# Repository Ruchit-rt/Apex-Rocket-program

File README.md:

# art-apex
PCBs and software for ART's APEX rocket

# Contents

1. [Hardware](#Hardware)
2. [Software architecture](#SoftwareArchitecture)
3. [Next Steps](#NextSteps)

## Hardware

The flight computer for Apex consists of the following components:

1. [Tiny2040](https://shop.pimoroni.com/products/tiny-2040) microcontroller - for controlling each of the components
2. [BNO085](https://learn.adafruit.com/adafruit-9-dof-orientation-imu-fusion-breakout-bno085) 9DoF IMU - for recording and fusing flight data
3. [DPS310](https://www.infineon.com/cms/en/product/sensor/pressure-sensors/pressure-sensors-for-iot/dps310/) barometer - for recording altitude information
4. [Sim800L](https://nettigo.eu/products/sim800l-gsm-grps-module) GPRS/GSM module - for communication between the flight computer and ground team
5. [Adafruit mini GPS PA1010D](https://www.adafruit.com/product/4415) GPS module - for recovery
6. 3.7V 200maH LiPo battery - for powering the system
7. A 104 decibel speaker - for recovery

The Tiny2040 is connected to the BNO085, DPS310 and PA1010D via an I2C connection using GPIO pins 26 and 27. The Tiny2040 is connected to the Sim800L module via a UART connection using GPIO pins 4 and 5.

The SIM8000L **must** be isolated when the Tiny2040 is connected to USB, or else it will be fried.

## Software

The filesystem on board the Tiny2040 will look like this:
```
📦src
 ┣ 📂lib
 ┃ ┣ 📂adafruit_bno08x
 ┃ ┃ ┣ 📜debug.py
 ┃ ┃ ┣ 📜i2c.py
 ┃ ┃ ┗ 📜__init__.py
 ┃ ┣ 📂adafruit_bus_device
 ┃ ┃ ┣ 📜i2c_device.mpy
 ┃ ┃ ┣ 📜spi_device.mpy
 ┃ ┃ ┗ 📜__init__.py
 ┃ ┣ 📂adafruit_register
 ┃ ┃ ┣ 📜i2c_bcd_alarm.mpy
 ┃ ┃ ┣ 📜i2c_bcd_datetime.mpy
 ┃ ┃ ┣ 📜i2c_bit.mpy
 ┃ ┃ ┣ 📜i2c_bits.mpy
 ┃ ┃ ┣ 📜i2c_struct.mpy
 ┃ ┃ ┣ 📜i2c_struct_array.mpy
 ┃ ┃ ┗ 📜__init__.py
 ┃ ┣ 📜adafruit_dps310.mpy
 ┃ ┗ 📜adafruit_gps.py
 ┣ 📜boot.py
 ┣ 📜code.py
 ┣ 📜gps.py
 ┣ 📜led.py
 ┣ 📜phone.number
 ┣ 📜sensors.py
 ┣ 📜sms.py
 ┣ 📜speaker.py
 ┗ 📜state_machine.py
```

All folders inside the lib directory are libraries required for the Tiny2040 to interact with components. None of these files should be changed, except for lib/adafruit_bno08x/\_\_init__.py, where `_DEFAULT_REPORT_INTERVAL` should be set to 35ms. **Pro tip: don't lower this if you want to launch**.

`boot.py` runs right after the Tiny2040 boots up. Its sole purpose is to grant write permission to the Tiny2040. Due to the implementation of CircuitPython's filesystem either a laptop or the Tiny2040, can write to the Tiny2040's filesystem, so this ensures that the Tiny2040 has this permission.

`code.py` runs the main code of the AAS. It essentially runs through the state machine defined in `state_machine.py`.

`gps.py`, `led.py`, `sensors.py`, `speaker.py` and `sms.py` are [adapters](https://www.tutorialspoint.com/design_pattern/adapter_pattern.htm) around the peripherals discussed above. The adapter pattern is used to decouple the rest of the code from the specifics of these devices.

`state_machine.py` contains the bulk of the flight logic. It describes a (linear) [finite state machine](https://en.wikipedia.org/wiki/Finite-state_machine) with 5 states.

1. Diagnostic - initialises sensors and sends initial messages
2. Calibration - calibrates the BNO085 as described [here](https://www.ceva-dsp.com/wp-content/uploads/2019/10/BNO080_085-Datasheet.pdf) on page 39
3. Preflight - sleeps until the launch command is sent.
4. Flight - records 5 minutes of flight data, and sends data to the telemetry service.
5. Postflight - sends the rocket's location/plays the siren when asked. Also plays the siren once every 30 seconds.

The Flight stage is the most involved, so a brief explanation of its code can be found below.

```py
def run(self):
    i = 0
    led.colour(255, 0, 0)

    #Problem:
    #Sim module will need long (50ms+) waits to work
    #But we can't afford that in a single threaded environment
    #Solution:
    #Use pkt_wait to provide the sleeps
    pkt_wait = 1
    pkt = bytearray(sensors.data_size * 4)
    self._sms.connect()

    while i < self._flight_time:
        pkt_wait -= 1
        i += 1
        start = millis()
        data = self._sensors.get()
        for reading in data:
            self._sensor_storage.write(struct.pack("f", reading))

        if pkt_wait == 0:
            pkt[0:4] = struct.pack("f", data[0]) #time
            for j in range(4):
                pkt[4*j:4*(j+1)] = struct.pack("f", data[j+4])
            
            pkt[20:24] = struct.pack("f", data[10]) #altitude
            pkt_wait = self._sms.send_pkt(pkt)
        end = millis()
        sleep_ms(max(0, self._delay - (end - start)))

    self._sensor_storage.flush()
    self._sensor_storage.close()
    self._sms.disconnect()
    return postflight(self._sms, self._gps)
```

```py
led.colour(255, 0, 0)
```
First the Tiny2040's led is set to red to indicate flight.

```py
pkt_wait = 1
pkt = bytearray(sensors.data_size * 4)
self._sms.connect()
```
This code relates to the telemetry service. The Sim800L will connect to GPRS here (the internet) and send appropriate data via UDP. To save space, it will group several readings into a single packet.

```py
while i < self._flight_time:
    pkt_wait -= 1
    i += 1
    start = millis()
    data = self._sensors.get()
    for reading in data:
        self._sensor_storage.write(struct.pack("f", reading))

    if pkt_wait == 0:
        pkt[0:4] = struct.pack("f", data[0]) #time
        for j in range(4):
            pkt[4*j:4*(j+1)] = struct.pack("f", data[j+4])
        
        pkt[20:24] = struct.pack("f", data[10]) #altitude
        pkt_wait = self._sms.send_pkt(pkt)
    end = millis()
    sleep_ms(max(0, self._delay - (end - start)))
```

This is the main flight loop. It waits for `self._flight_time` readings to occur (assuming each reading takes at most `self._delay` ms).

```py
start = millis()
data = self._sensors.get()
for reading in data:
    self._sensor_storage.write(struct.pack("f", reading))
```
This code takes sensor readings, and records the time that they were taken, then writes them into a file. The values are stored as 32bit floating point numbers, to save space.
Note: the time recorded is milliseconds from the start.

```py
if pkt_wait == 0:
    pkt[0:4] = struct.pack("f", data[0]) #time
    for j in range(4):
        pkt[4*j:4*(j+1)] = struct.pack("f", data[j+4])
    
    pkt[20:24] = struct.pack("f", data[10]) #altitude
    pkt_wait = self._sms.send_pkt(pkt)
```
This adds the readings into the packet defined earlier, and if the packet is full it sends them.

The `pkt_wait` variable is used to solve a problem, which is that the Sim800l needs to wait around 200ms after it's sent a packet, before being able to send another one. However we can't perform this wait in the main loop, as that would lead to large delays in between recordings, so we define the `pkt_wait` variable to indicate whether we can send a packet. This allows us to use the main loop as a pseudo sleep (at the time of writing, the `uasynchio` library was not available).

```py
end = millis()
sleep_ms(max(0, self._delay - (end - start)))
```
This ensures that we always sleep for at least 50ms, regardless of how long different components take to work.

```py
self._sensor_storage.flush()
self._sensor_storage.close()
self._sms.disconnect()
return postflight(self._sms, self._gps)
```
Finally we flush the recordings, and close the file, then disconnect the Sim800L from GPRS and move on to the postflight stage. 

The end.

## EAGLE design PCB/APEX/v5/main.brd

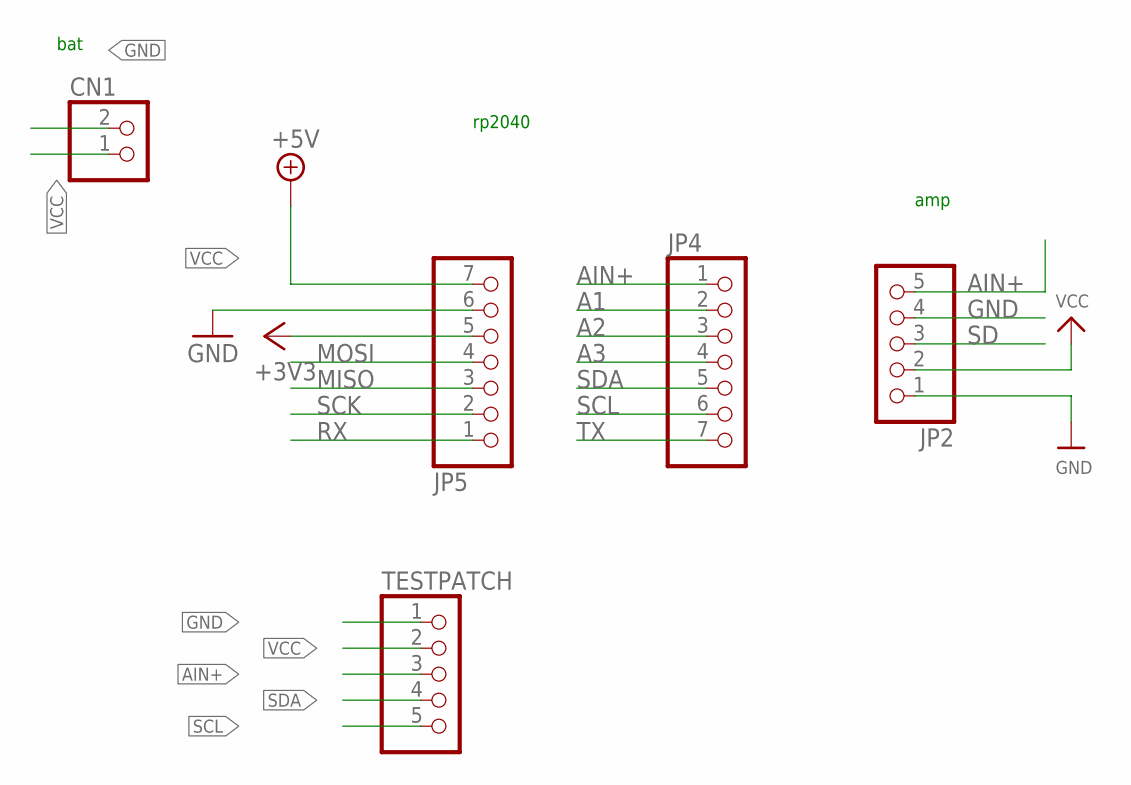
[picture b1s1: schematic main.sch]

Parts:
CN1: JST_2PIN-THM; JST-PH-2-THM
JP2: HEADER-1X570MIL; 1X05_ROUND_70
JP4, JP5: HEADER-1X7; 1X07_OVAL
TESTPATCH: PINHD-1X5; 1X05

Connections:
+3V3: JP5.5
A1: JP4.2
A2: JP4.3
A3: JP4.4
AIN+: JP2.5, JP4.1, TESTPATCH.3
GND: CN1.2 (1), JP2.1, JP2.4, JP5.6, TESTPATCH.1
MISO: JP5.3
MOSI: JP5.4
RX: JP5.1
SCK: JP5.2
SCL: JP4.6, TESTPATCH.5
SD: JP2.3
SDA: JP4.5, TESTPATCH.4
TX: JP4.7
VCC: CN1.1 (2), JP2.2, JP5.7, TESTPATCH.2

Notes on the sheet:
amp
bat
rp2040

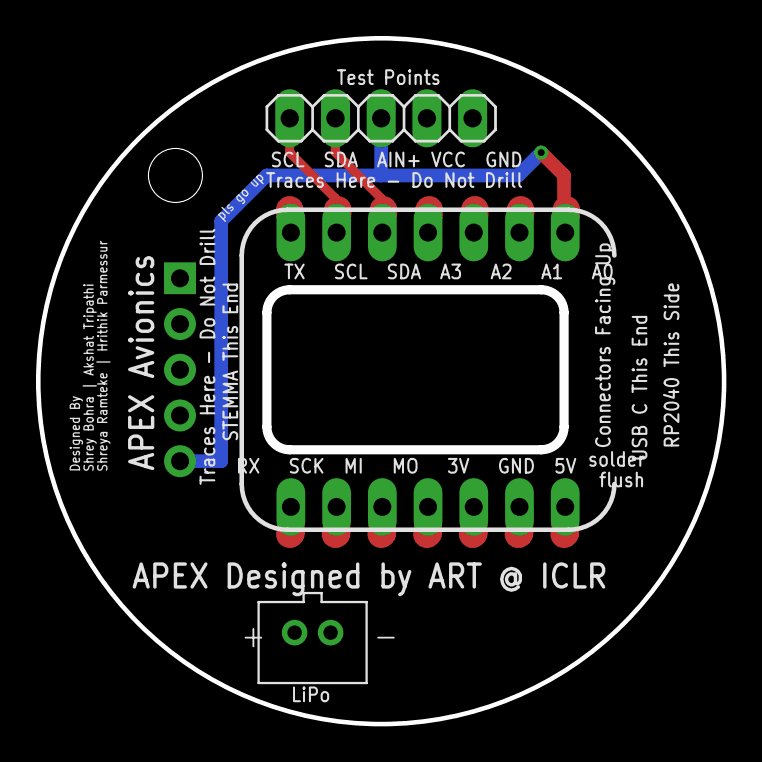
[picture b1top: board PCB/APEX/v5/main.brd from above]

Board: 2 copper layers, 38.1 x 38.1 mm, 5 parts (1 on the bottom side), 5 nets.

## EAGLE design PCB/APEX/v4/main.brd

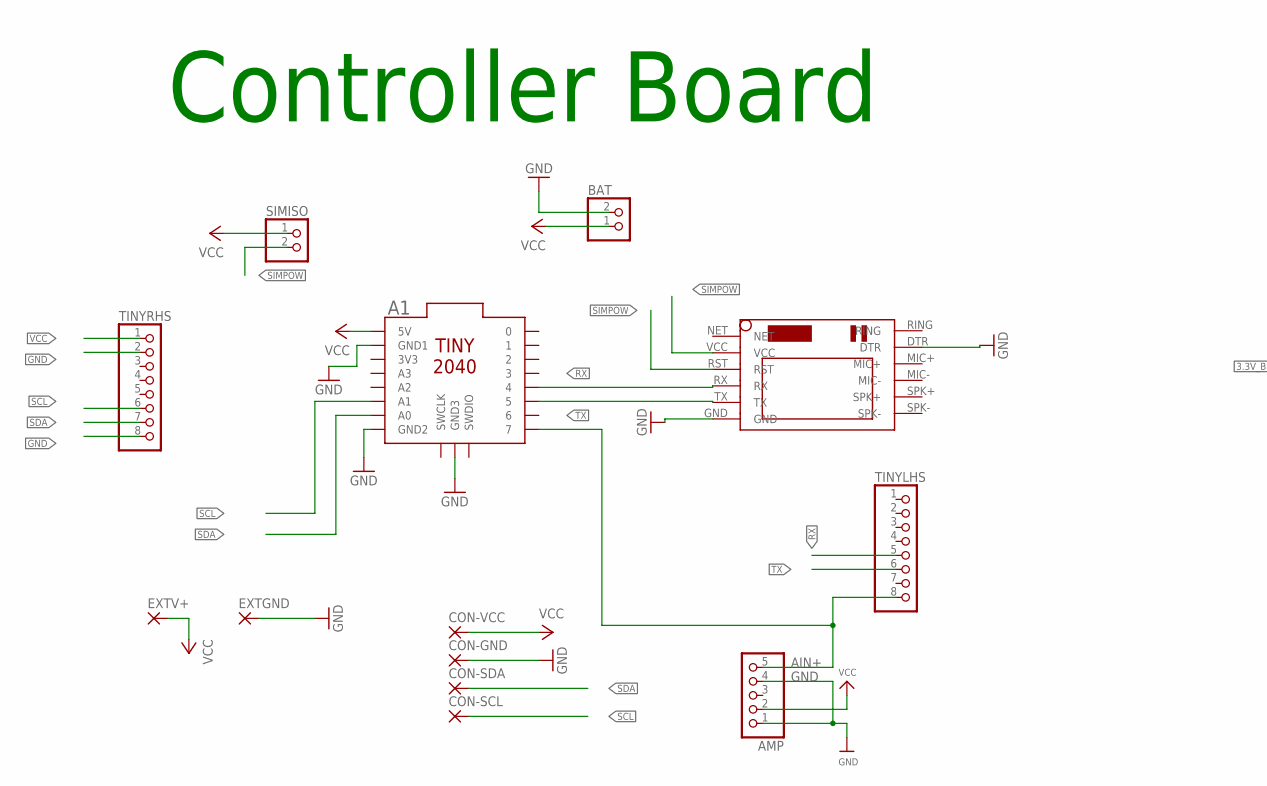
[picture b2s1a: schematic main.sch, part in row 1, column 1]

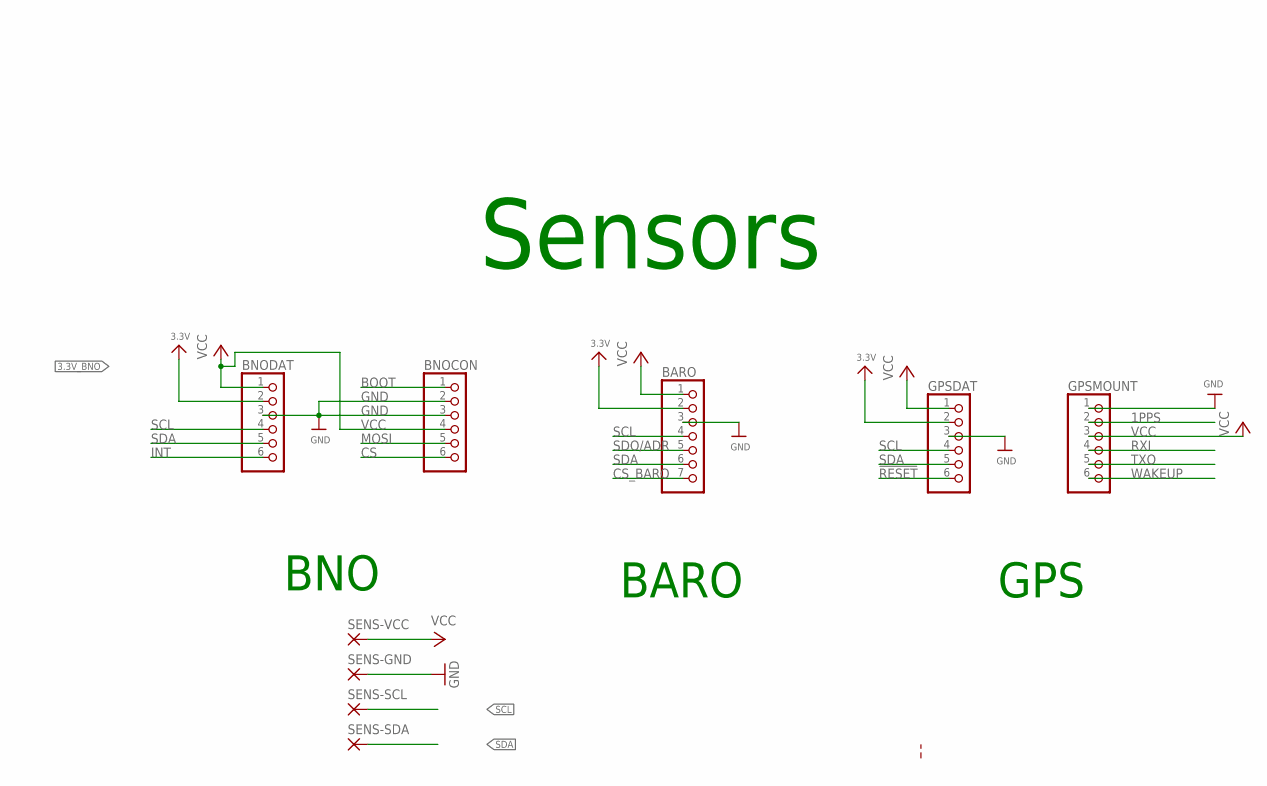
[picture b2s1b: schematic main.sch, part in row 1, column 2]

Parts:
A1: TINY2040
AMP: HEADER-1X570MIL; 1X05_ROUND_70
BARO: HEADER-1X770MIL; 1X07_ROUND_70
BAT: JST_2PIN-THM-RA; JST-PH-2-THM-RA
BNOCON: HEADER-1X670MIL; 1X06_ROUND_70
BNODAT: HEADER-1X670MIL; 1X06_ROUND_70
CON-GND: 3,17/1,3
CON-SCL: 3,17/1,3
CON-SDA: 3,17/1,3
CON-VCC: 3,17/1,3
EXTGND: SMD5; SMD2,54-5,08
EXTV+: SMD5; SMD2,54-5,08
GPSDAT: HEADER-1X670MIL; 1X06_ROUND_70
GPSMOUNT: HEADER-1X670MIL; 1X06_ROUND_70
SENS-GND: 3,17/1,3
SENS-SCL: 3,17/1,3
SENS-SDA: 3,17/1,3
SENS-VCC: 3,17/1,3
SIMISO: PINHD-1X2; 1X02
TINYLHS: PINHD-1X8; 1X08
TINYRHS: PINHD-1X8; 1X08
U$1: SIM800LMODULE

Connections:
1PPS: GPSMOUNT.2
3.3V_2: BARO.2
3.3V_3: GPSDAT.2
3.3V_BNO: BNODAT.2
!RESET: GPSDAT.6
AIN+: A1.7, AMP.5, TINYLHS.8
BOOT: BNOCON.1
CS: BNOCON.6
CS_BARO: BARO.7
GND: A1.GND1, A1.GND2, A1.GND3, AMP.1, AMP.4, BARO.3, BAT.2 (1), BNOCON.2, BNOCON.3, BNODAT.3, CON-GND.1, EXTGND.1, GPSDAT.3, GPSMOUNT.1, SENS-GND.1, TINYRHS.2, TINYRHS.8, U$1.DTR, U$1.GND
INT: BNODAT.6
MOSI: BNOCON.5
RX: A1.4, TINYLHS.5, U$1.RX
RXI: GPSMOUNT.4
SCL: A1.A1, BARO.4, BNODAT.4, CON-SCL.1, GPSDAT.4, SENS-SCL.1, TINYRHS.6
SDA: A1.A0, BARO.6, BNODAT.5, CON-SDA.1, GPSDAT.5, SENS-SDA.1, TINYRHS.7
SDO/ADR: BARO.5
SIMPOW: SIMISO.2, U$1.RST, U$1.VCC
TX: A1.5, TINYLHS.6, U$1.TX
TXO: GPSMOUNT.5
VCC: A1.5V, AMP.2, BARO.1, BAT.1 (2), BNOCON.4, BNODAT.1, CON-VCC.1, EXTV+.1, GPSDAT.1, GPSMOUNT.3, SENS-VCC.1, SIMISO.1, TINYRHS.1
WAKEUP: GPSMOUNT.6

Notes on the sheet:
Controller Board
BNO
BARO
GPS
Sensors

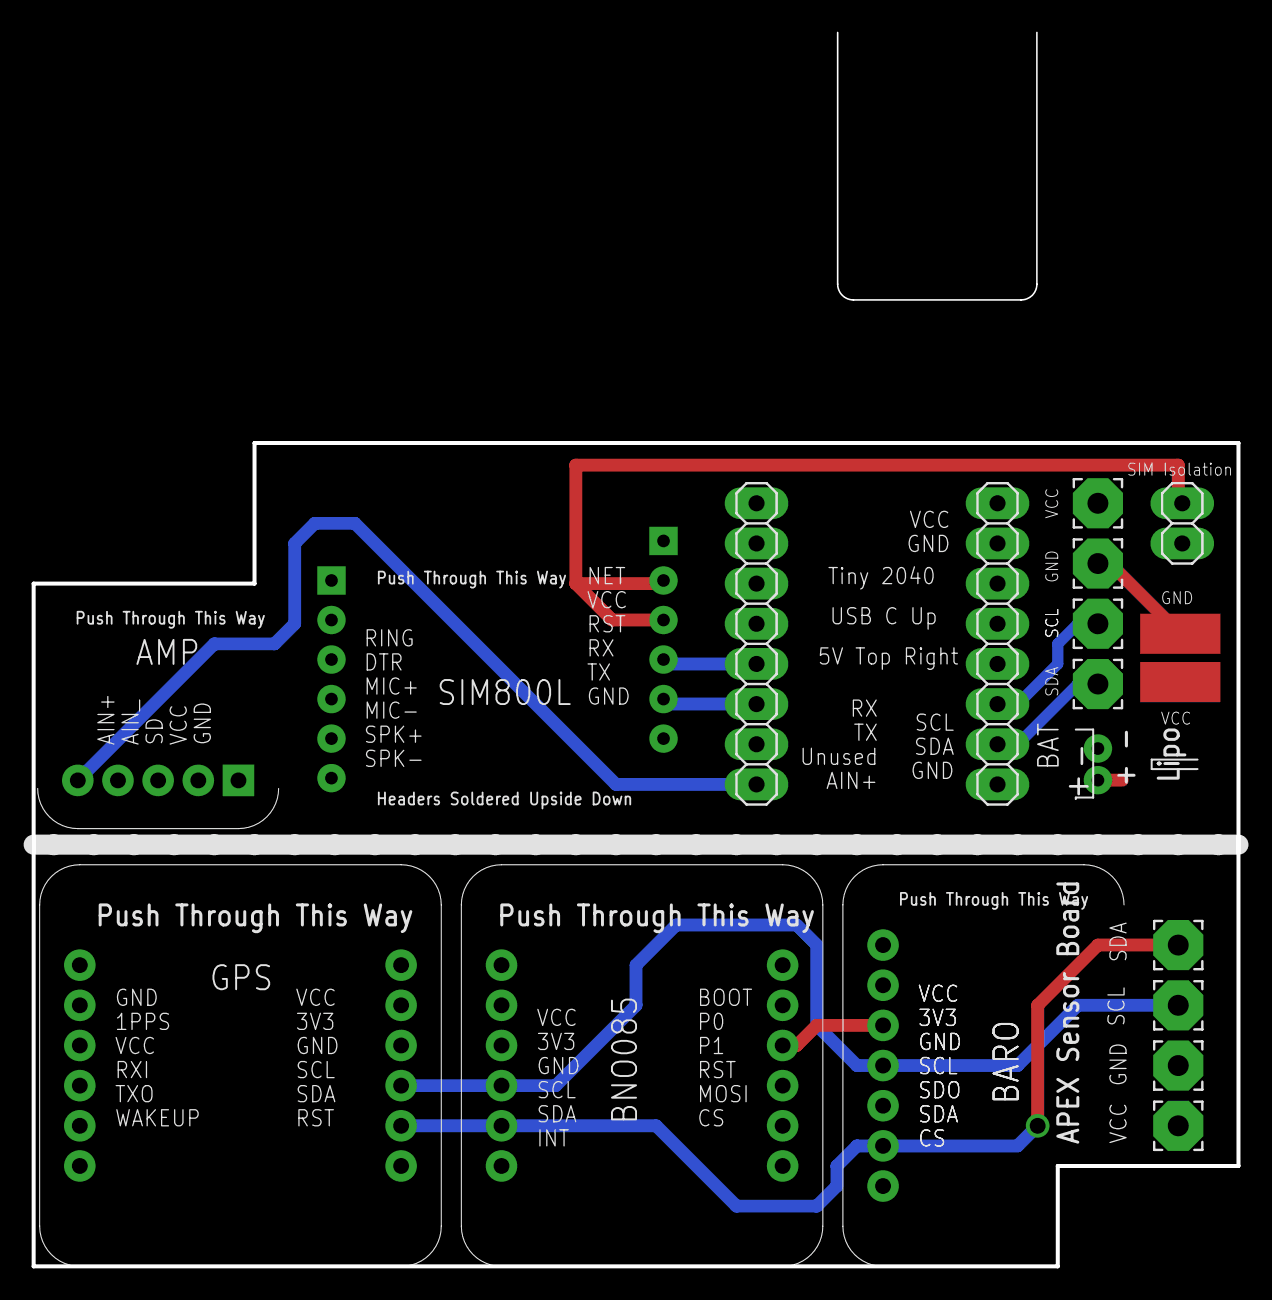
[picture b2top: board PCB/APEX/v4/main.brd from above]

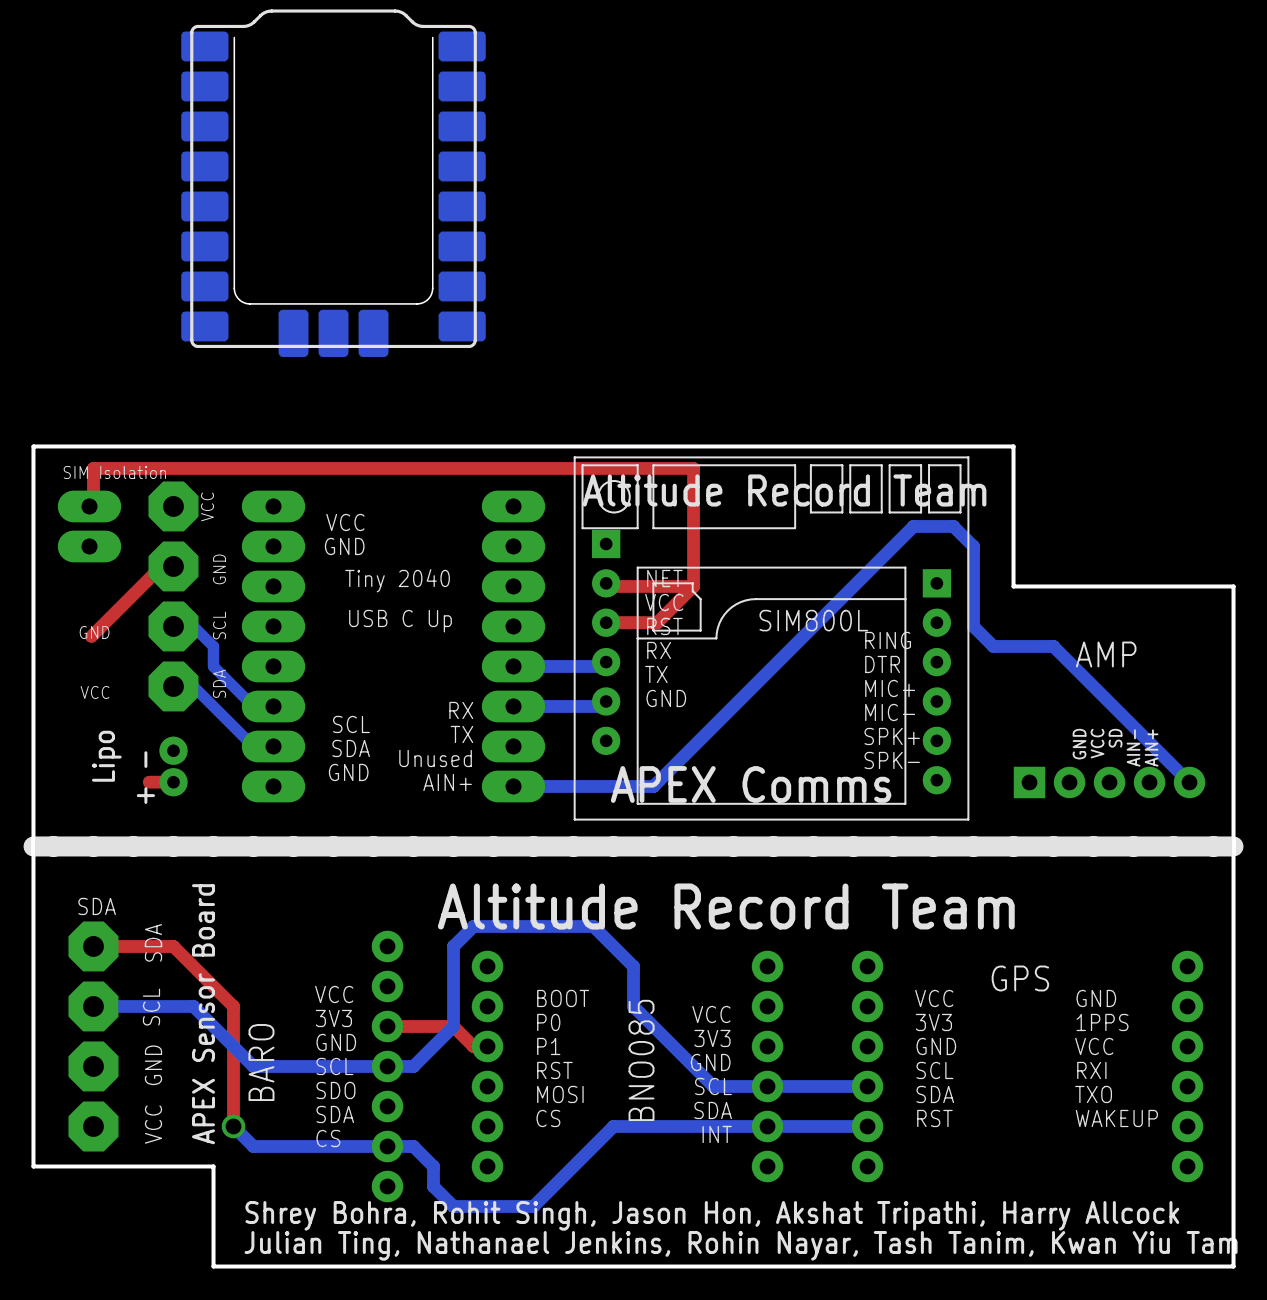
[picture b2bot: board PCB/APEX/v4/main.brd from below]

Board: 2 copper layers, 76.2 x 52.1 mm, 22 parts (4 on the bottom side), 8 nets.

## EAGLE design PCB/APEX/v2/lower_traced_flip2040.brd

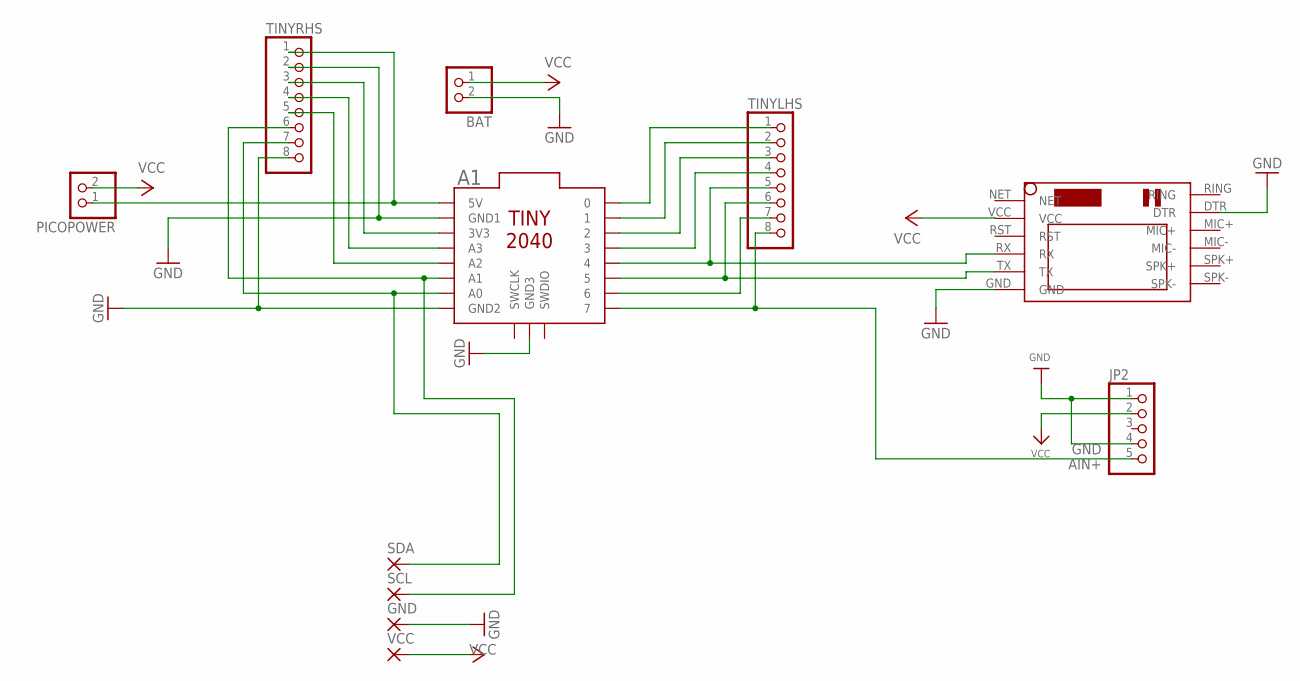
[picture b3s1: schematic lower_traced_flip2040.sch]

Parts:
A1: TINY2040
BAT: JST_2PIN-THM-RA; JST-PH-2-THM-RA
GND: 3,17/1,1
JP2: HEADER-1X570MIL; 1X05_ROUND_70
PICOPOWER: PINHD-1X2; 1X02
SCL: 3,17/1,1
SDA: 3,17/1,1
TINYLHS: PINHD-1X8; 1X08
TINYRHS: PINHD-1X8; 1X08
U$2: SIM800LMODULE
VCC: 3,17/1,1

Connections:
AIN+: A1.7, JP2.5, TINYLHS.8
GND: A1.GND1, A1.GND2, A1.GND3, BAT.2 (1), GND.1, JP2.1, JP2.4, TINYRHS.2, TINYRHS.8, U$2.DTR, U$2.GND
unnamed: A1.4, TINYLHS.5, U$2.RX
unnamed: A1.5, TINYLHS.6, U$2.TX
unnamed: A1.A1, SCL.1, TINYRHS.6
unnamed: A1.A0, SDA.1, TINYRHS.7
unnamed: A1.5V, PICOPOWER.1, TINYRHS.1
unnamed: A1.6, TINYLHS.7
unnamed: A1.3, TINYLHS.4
unnamed: A1.2, TINYLHS.3
unnamed: A1.1, TINYLHS.2
unnamed: A1.0, TINYLHS.1
unnamed: A1.A2, TINYRHS.5
unnamed: A1.A3, TINYRHS.4
unnamed: A1.3V3, TINYRHS.3
VCC: BAT.1 (2), JP2.2, PICOPOWER.2, U$2.VCC, VCC.1

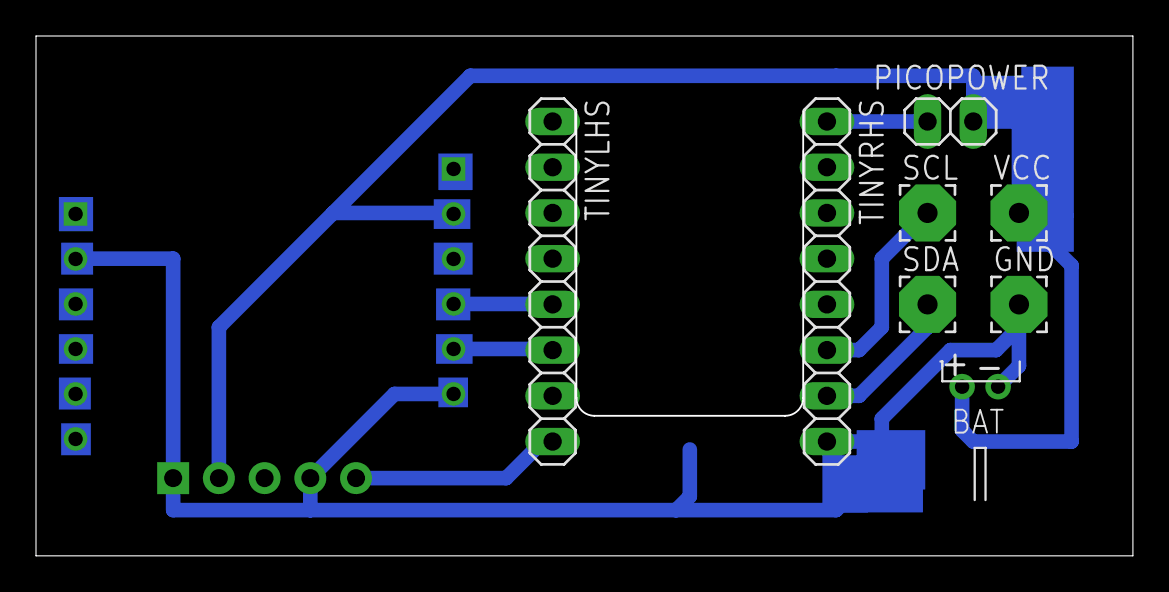
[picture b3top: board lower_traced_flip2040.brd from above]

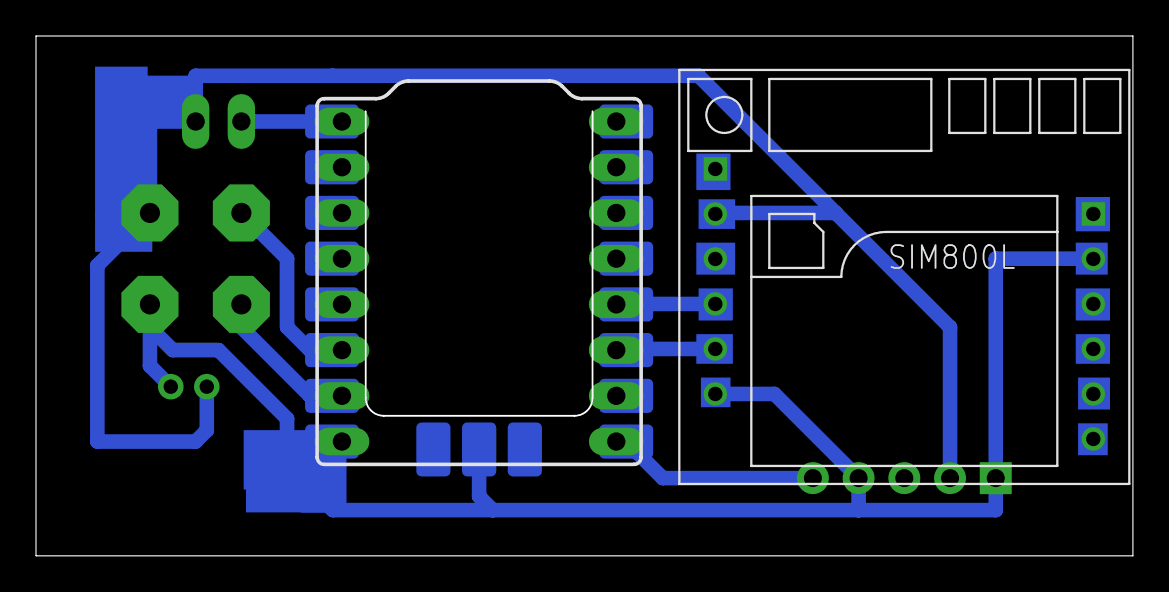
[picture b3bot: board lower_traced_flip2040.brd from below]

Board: 2 copper layers, 60.9 x 28.9 mm, 11 parts (3 on the bottom side), 16 nets.

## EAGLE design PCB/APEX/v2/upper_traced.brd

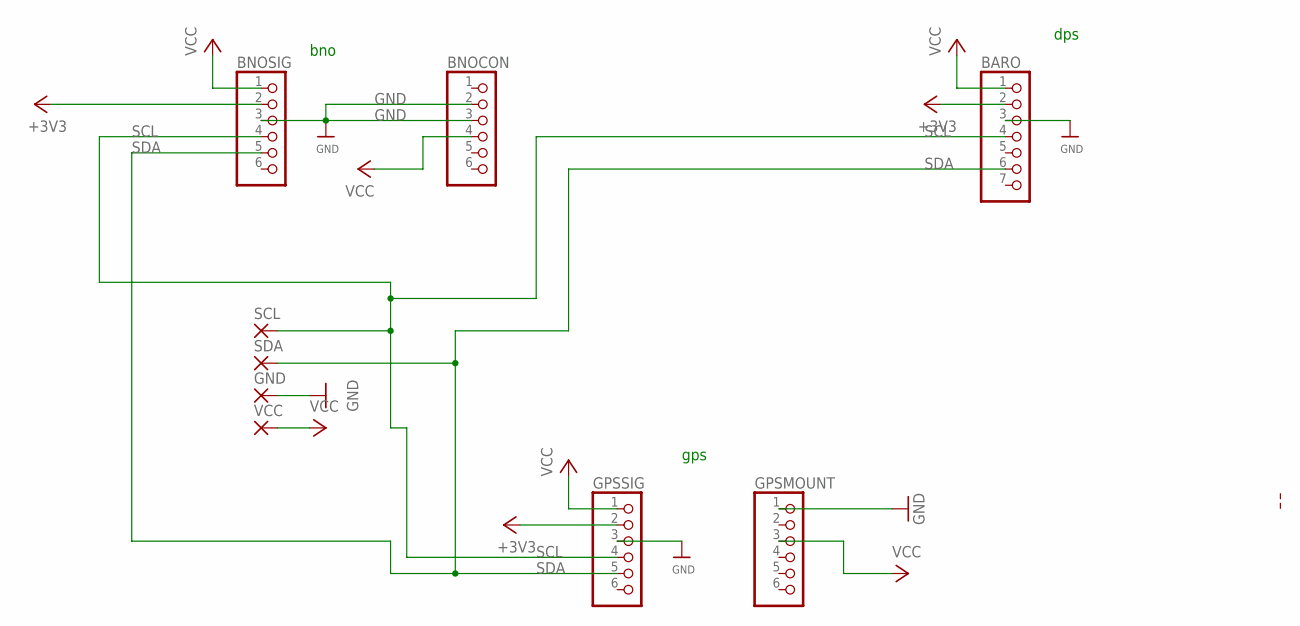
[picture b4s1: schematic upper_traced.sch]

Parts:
BARO: HEADER-1X770MIL; 1X07_ROUND_70
BNOCON: HEADER-1X670MIL; 1X06_ROUND_70
BNOSIG: HEADER-1X670MIL; 1X06_ROUND_70
GND: 3,17/1,1
GPSMOUNT: HEADER-1X670MIL; 1X06_ROUND_70
GPSSIG: HEADER-1X670MIL; 1X06_ROUND_70
SCL: 3,17/1,1
SDA: 3,17/1,1
VCC: 3,17/1,1

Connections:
+3V3: BARO.2, BNOSIG.2, GPSSIG.2
GND: BARO.3, BNOCON.2, BNOCON.3, BNOSIG.3, GND.1, GPSMOUNT.1, GPSSIG.3
SCL: BARO.4, BNOSIG.4, GPSSIG.4, SCL.1
SDA: BARO.6, BNOSIG.5, GPSSIG.5, SDA.1
VCC: BARO.1, BNOCON.4, BNOSIG.1, GPSMOUNT.3, GPSSIG.1, VCC.1

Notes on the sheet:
bno
dps
gps

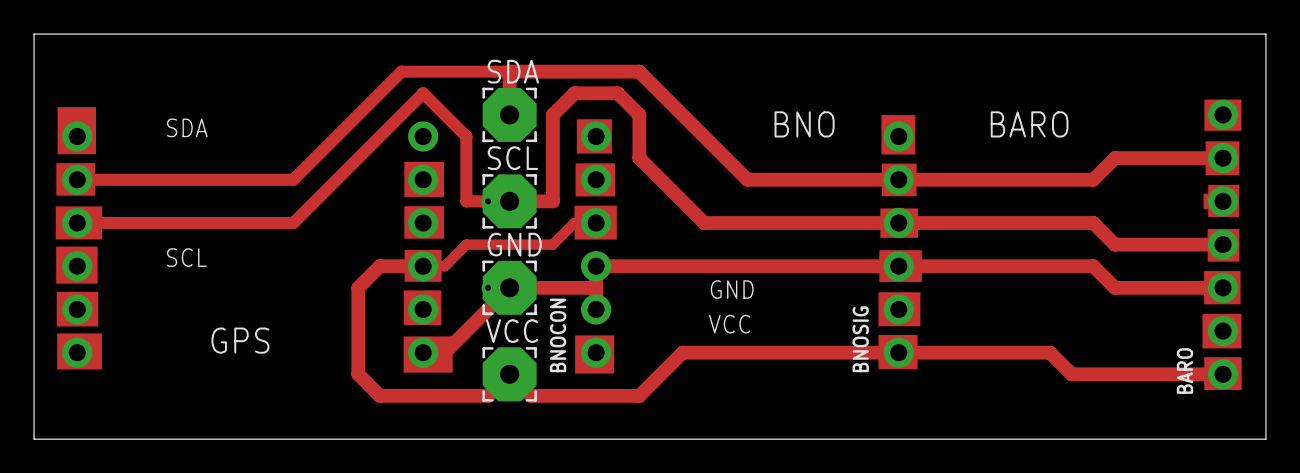
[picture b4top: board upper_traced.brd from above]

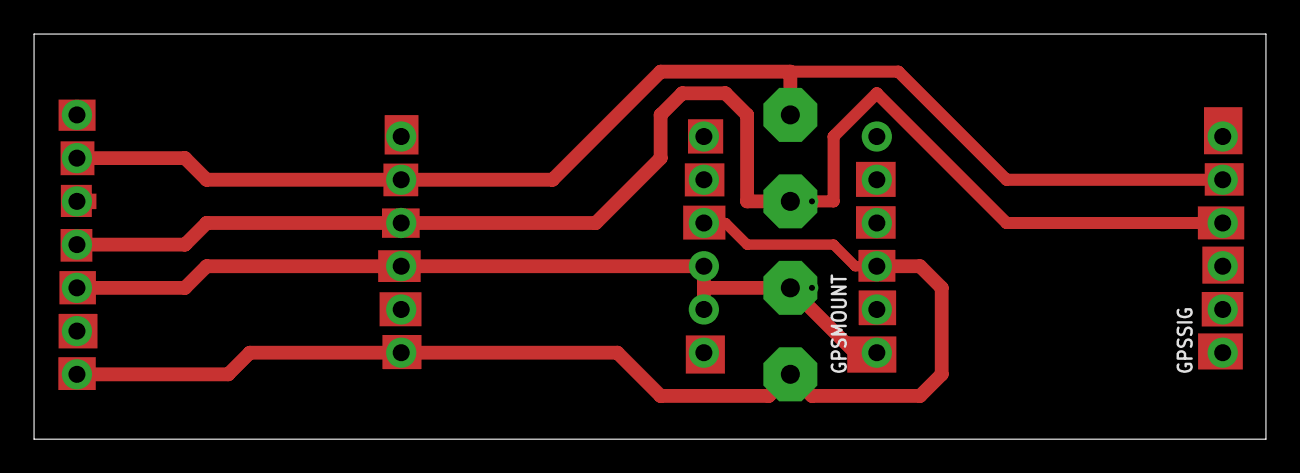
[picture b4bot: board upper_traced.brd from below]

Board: 2 copper layers, 72.4 x 23.8 mm, 9 parts (2 on the bottom side), 5 nets.

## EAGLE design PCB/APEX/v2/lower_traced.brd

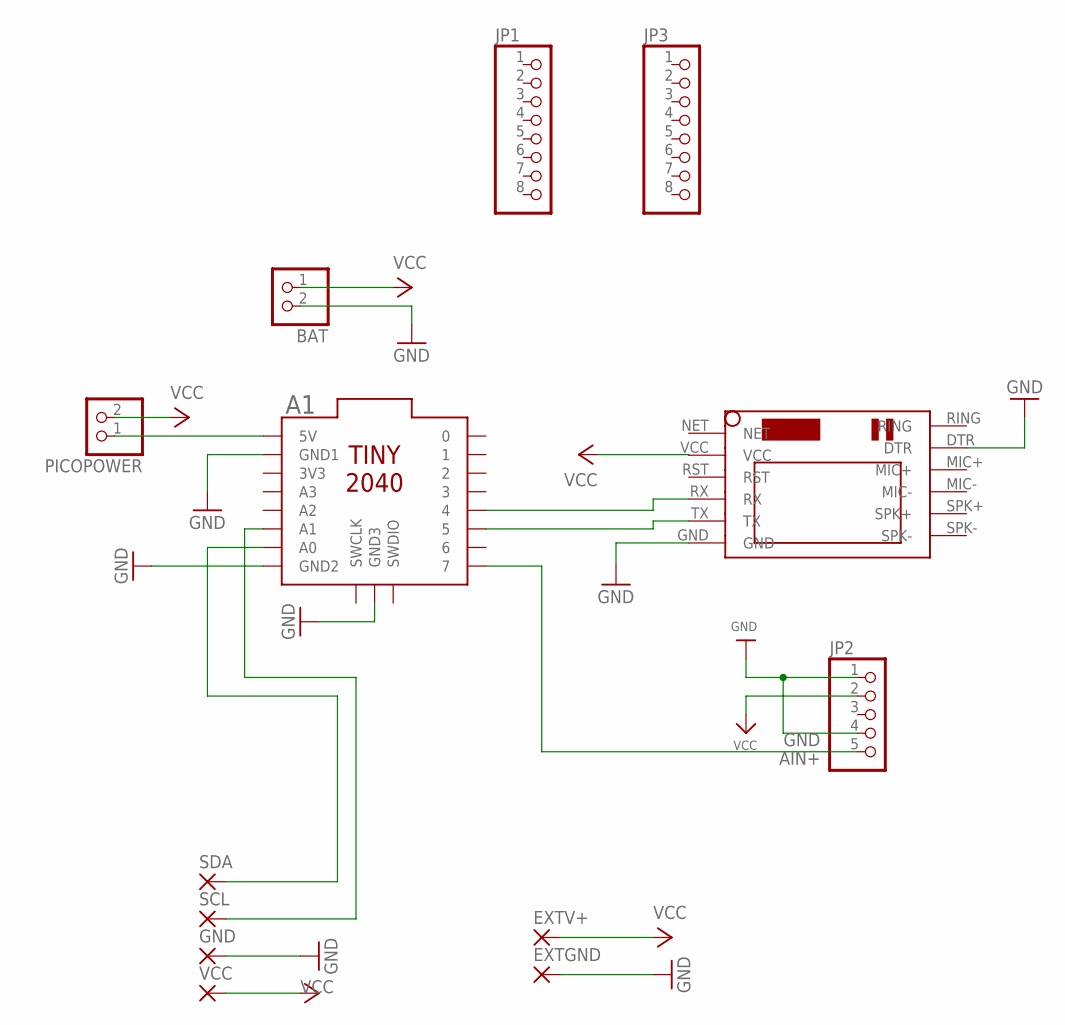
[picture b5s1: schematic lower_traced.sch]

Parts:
A1: TINY2040
BAT: JST_2PIN-THM-RA; JST-PH-2-THM-RA
EXTGND: SMD5; SMD2,54-5,08
EXTV+: SMD5; SMD2,54-5,08
GND: 3,17/1,1
JP1, JP3: PINHD-1X8; 1X08
JP2: HEADER-1X570MIL; 1X05_ROUND_70
PICOPOWER: PINHD-1X2; 1X02
SCL: 3,17/1,1
SDA: 3,17/1,1
U$2: SIM800LMODULE
VCC: 3,17/1,1

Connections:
AIN+: A1.7, JP2.5
GND: A1.GND1, A1.GND2, A1.GND3, BAT.2 (1), EXTGND.1, GND.1, JP2.1, JP2.4, U$2.DTR, U$2.GND
unnamed: A1.4, U$2.RX
unnamed: A1.5, U$2.TX
unnamed: A1.A1, SCL.1
unnamed: A1.A0, SDA.1
unnamed: A1.5V, PICOPOWER.1
VCC: BAT.1 (2), EXTV+.1, JP2.2, PICOPOWER.2, U$2.VCC, VCC.1

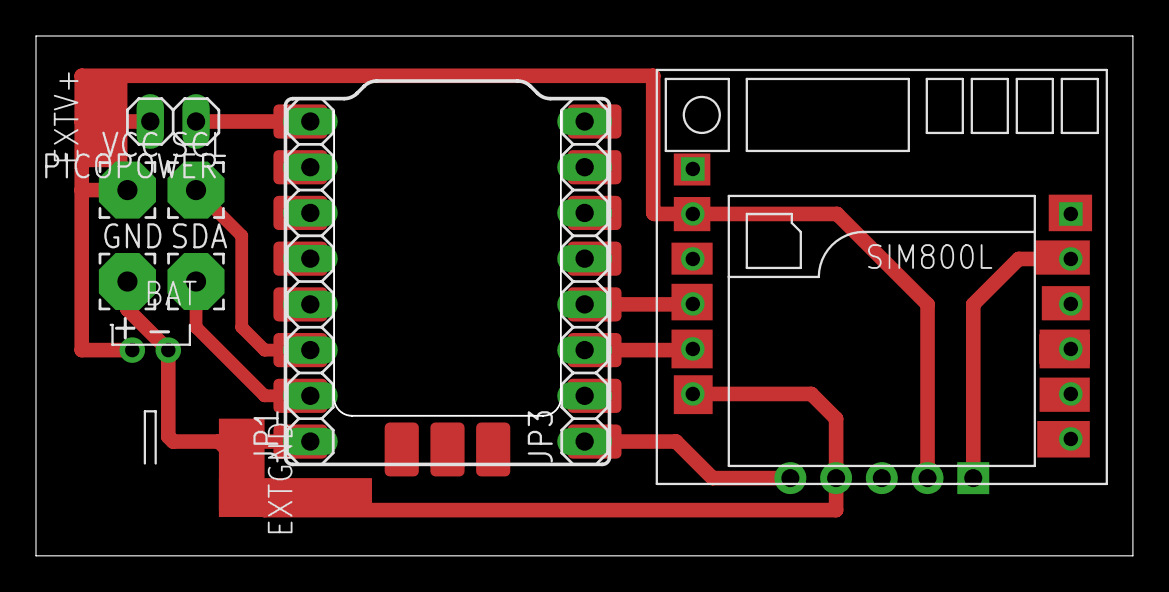
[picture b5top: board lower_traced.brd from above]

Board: 2 copper layers, 60.9 x 28.9 mm, 13 parts (0 on the bottom side), 8 nets.

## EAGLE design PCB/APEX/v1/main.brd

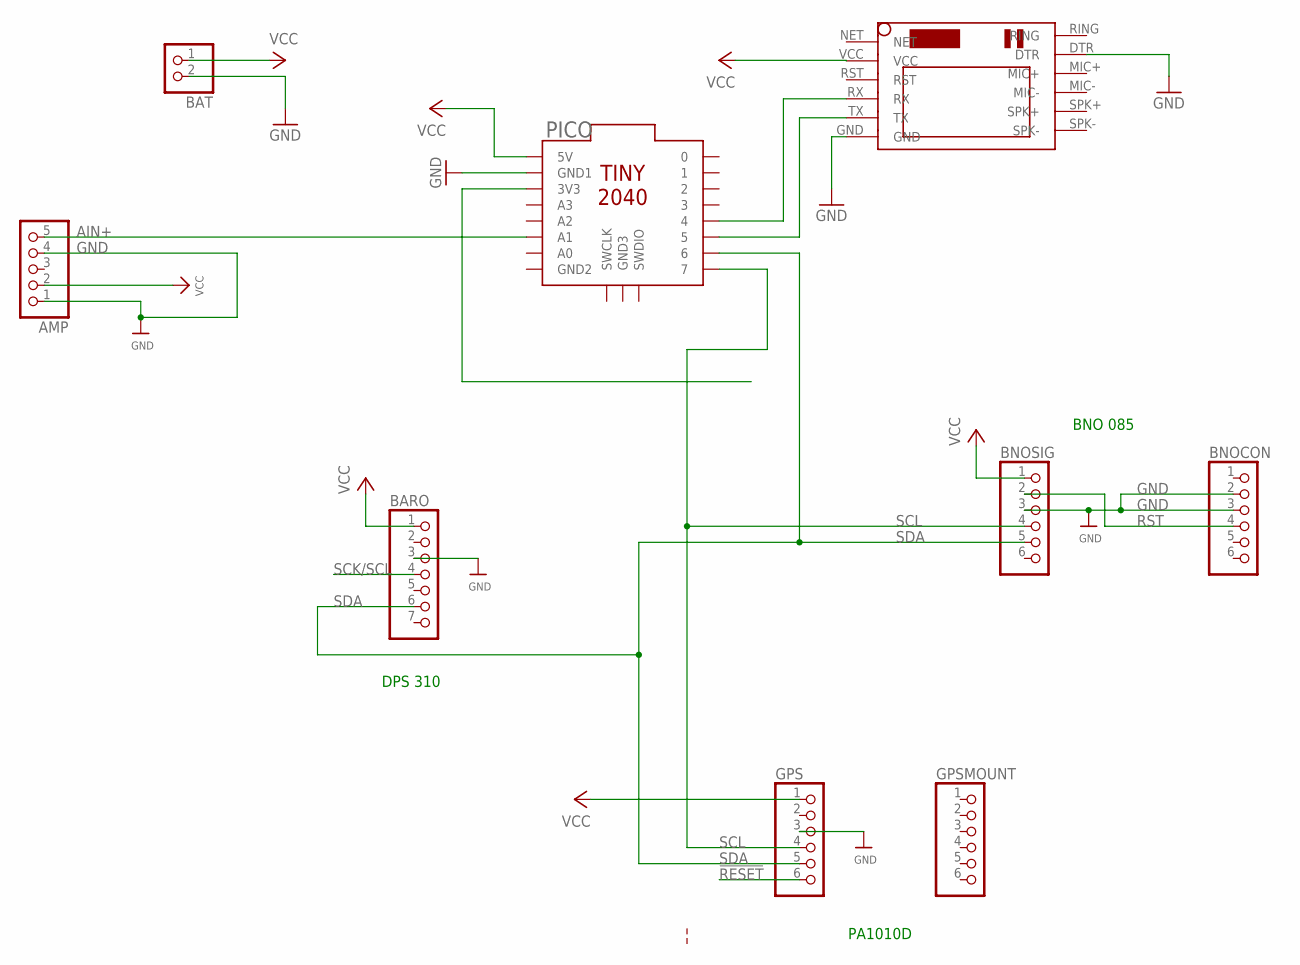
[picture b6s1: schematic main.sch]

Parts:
AMP: HEADER-1X570MIL; 1X05_ROUND_70
BARO: HEADER-1X770MIL; 1X07_ROUND_70
BAT: JST_2PIN-THM-RA; JST-PH-2-THM-RA
BNOCON: HEADER-1X670MIL; 1X06_ROUND_70
BNOSIG: HEADER-1X670MIL; 1X06_ROUND_70
GPS: HEADER-1X670MIL; 1X06_ROUND_70
GPSMOUNT: HEADER-1X670MIL; 1X06_ROUND_70
PICO: TINY2040
SIM: SIM800LMODULE

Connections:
!RESET: GPS.6
AIN+: AMP.5, PICO.A1
GND: AMP.1, AMP.4, BARO.3, BAT.2 (1), BNOCON.2, BNOCON.3, BNOSIG.3, GPS.3, PICO.GND1, SIM.DTR, SIM.GND
unnamed: PICO.4, SIM.RX
unnamed: PICO.5, SIM.TX
RST: BNOCON.4, BNOSIG.2
SCK/SCL: BARO.4
SCL: BNOSIG.4, GPS.4, PICO.7
SDA: BARO.6, BNOSIG.5, GPS.5, PICO.6
VCC: AMP.2, BARO.1, BAT.1 (2), BNOSIG.1, GPS.1, PICO.5V, SIM.VCC

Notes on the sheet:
BNO 085
DPS 310
PA1010D

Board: 2 copper layers, 9 parts (0 on the bottom side), 8 nets, no tracks yet.

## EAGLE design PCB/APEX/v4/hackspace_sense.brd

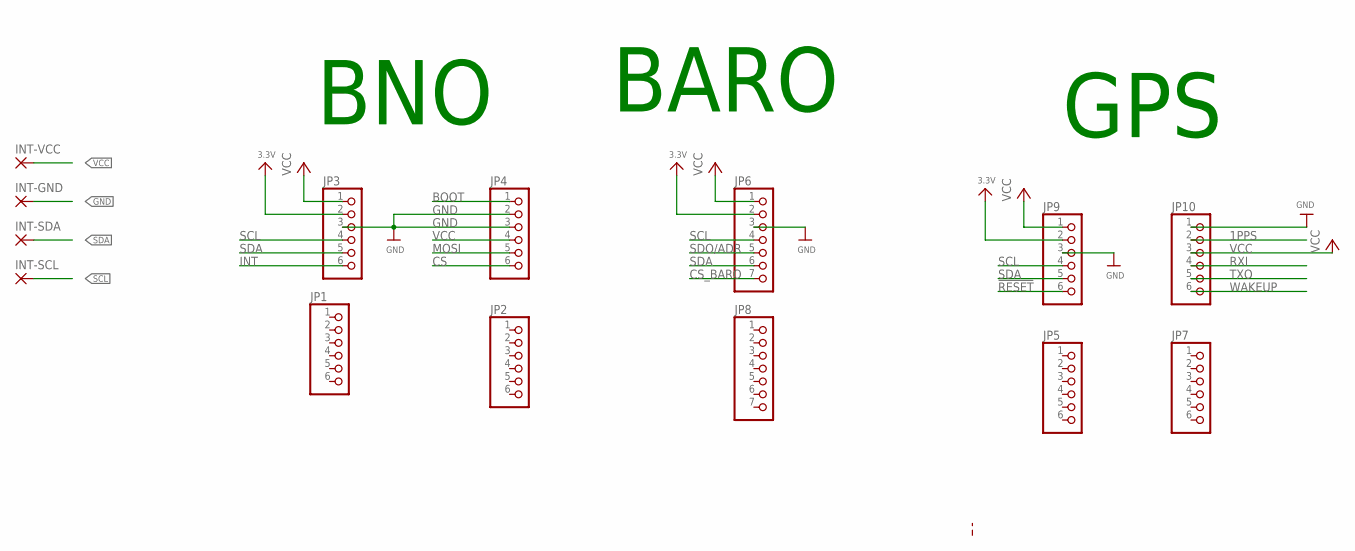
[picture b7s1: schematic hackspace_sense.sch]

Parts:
INT-GND: 3,17/1,1
INT-SCL: 3,17/1,1
INT-SDA: 3,17/1,1
INT-VCC: 3,17/1,1
JP1, JP2, JP5, JP7: PINHD-1X6; 1X06
JP3, JP4, JP9, JP10: HEADER-1X670MIL; 1X06_ROUND_70
JP6: HEADER-1X770MIL; 1X07_ROUND_70
JP8: PINHD-1X7; 1X07

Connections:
1PPS: JP10.2
3.3V_BARO: JP6.2
3.3V_BNO: JP3.2
3.3V_GPS: JP9.2
!RESET: JP9.6
BOOT: JP4.1
CS: JP4.6
CS_BARO: JP6.7
GND: INT-GND.1, JP3.3, JP4.2, JP4.3, JP6.3, JP9.3, JP10.1
INT: JP3.6
MOSI: JP4.5
RXI: JP10.4
SCL: INT-SCL.1, JP3.4, JP6.4, JP9.4
SDA: INT-SDA.1, JP3.5, JP6.6, JP9.5
SDO/ADR: JP6.5
TXO: JP10.5
VCC: INT-VCC.1, JP3.1, JP4.4, JP6.1, JP9.1, JP10.3
WAKEUP: JP10.6

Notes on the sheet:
BNO
BARO
GPS

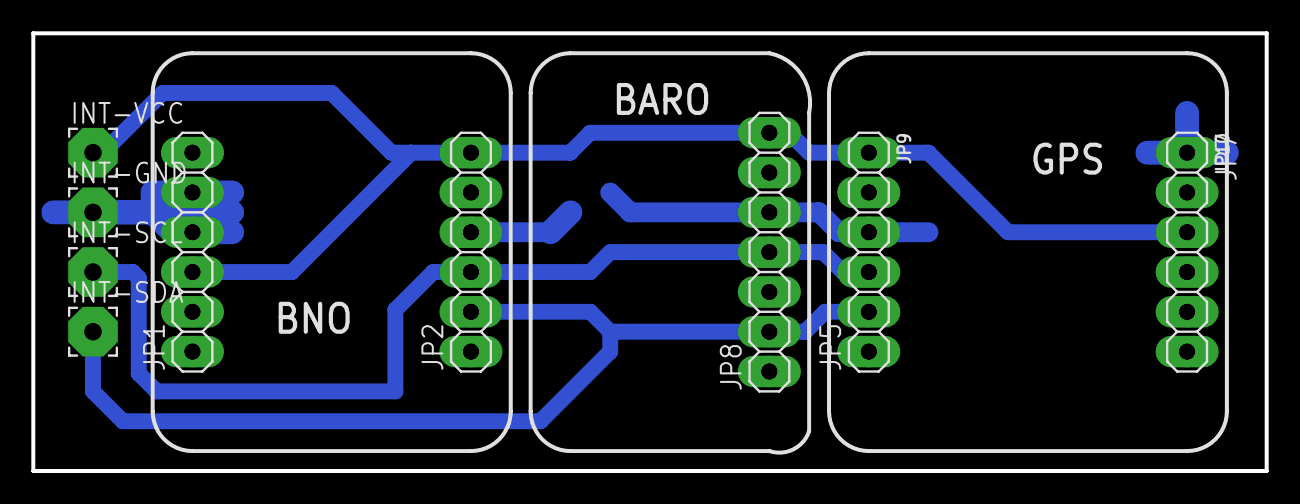
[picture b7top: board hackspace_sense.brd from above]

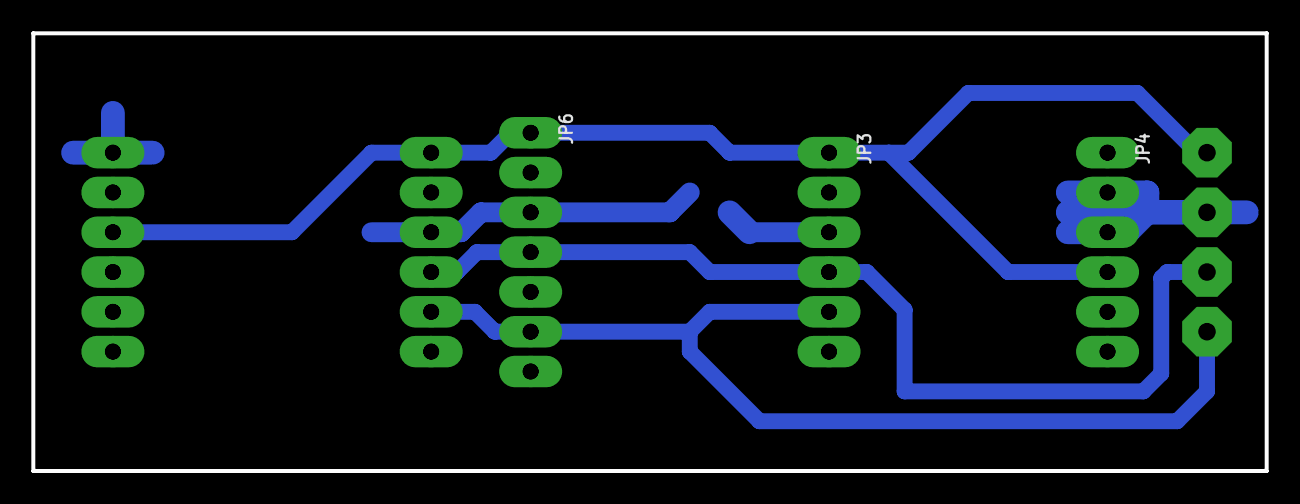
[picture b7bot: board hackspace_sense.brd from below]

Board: 2 copper layers, 78.7 x 27.9 mm, 14 parts (3 on the bottom side), 4 nets.

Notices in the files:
parts and their libraries:
microbuilder: This work is placed in the public domain, and may be freely used for commercial and non-commercial work with the following conditions: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
